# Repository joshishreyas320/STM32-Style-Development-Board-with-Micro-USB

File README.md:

# STM32-Style Development Board with Micro USB

> KiCad PCB Design | 2-Layer Board | ATmega328P-M + Micro USB

---

## Project Description
An Arduino-compatible MCU development board designed using **KiCad**, featuring an **ATmega328P-M** microcontroller, **Micro USB** interface for power and programming, and an **LM1117DT-5V** onboard voltage regulator. Dual 15-pin expansion headers provide full GPIO access in an Arduino-compatible footprint. Includes SMD resonator, power LED, and reset switch.

**Short Description (≤350 chars):**
> Arduino-compatible MCU development board with Micro USB interface, LM1117 5V regulation, dual 15-pin headers, and onboard LED+reset. Designed in KiCad with ATmega328P-M for embedded development use.

---

## Key Components

| Component | Description |
|-----------|-------------|
| **ATmega328P-M** | Core MCU – Arduino-compatible |
| **USB_B_Micro** | Micro USB connector for power and programming |
| **LM1117DT-5.0** | 5V LDO regulator from USB VBUS |
| **SMD Resonator (3-pin)** | Stable MCU clock source |
| **2× 15-pin Headers** | GPIO/power expansion (Arduino-style) |
| **Reset Switch** | Manual MCU reset |
| **LED** | Power indicator |
| **Decoupling Capacitors** | +3.3V and +5V rail filtering |

---

## Design Features
- Micro USB for both power supply and MCU programming
- LM1117DT-5.0 provides regulated 5V from USB VBUS
- ATmega328P-M with Arduino-compatible pinout
- SMD resonator for reliable clock without external components
- Compact 2-layer PCB with dual 15-pin expansion headers
- Onboard power LED and reset switch for user interaction

---

## Signal Flow
```
Micro USB Connector (VBUS / D+ / D-)
       ↓
  LM1117DT-5.0 – Voltage Regulator (5V)
       ↓
  ATmega328P-M – MCU
       ↓
  SMD Resonator ← Clock Source
  15-pin Dual Headers ← GPIO / Power Expansion
  LED ← Power Indicator
  Reset Switch ← Manual Reset
```

---

## Files Included
- Development_board_project_with_STM_components_and_Micro_USB.kicad_sch – Schematic
- Development_board_project_with_STM_components_and_Micro_USB.kicad_pcb – PCB Layout
- Gerber_File_Development_board_project_with_STM_components_and_Micro_USB.zip – Gerber files

---

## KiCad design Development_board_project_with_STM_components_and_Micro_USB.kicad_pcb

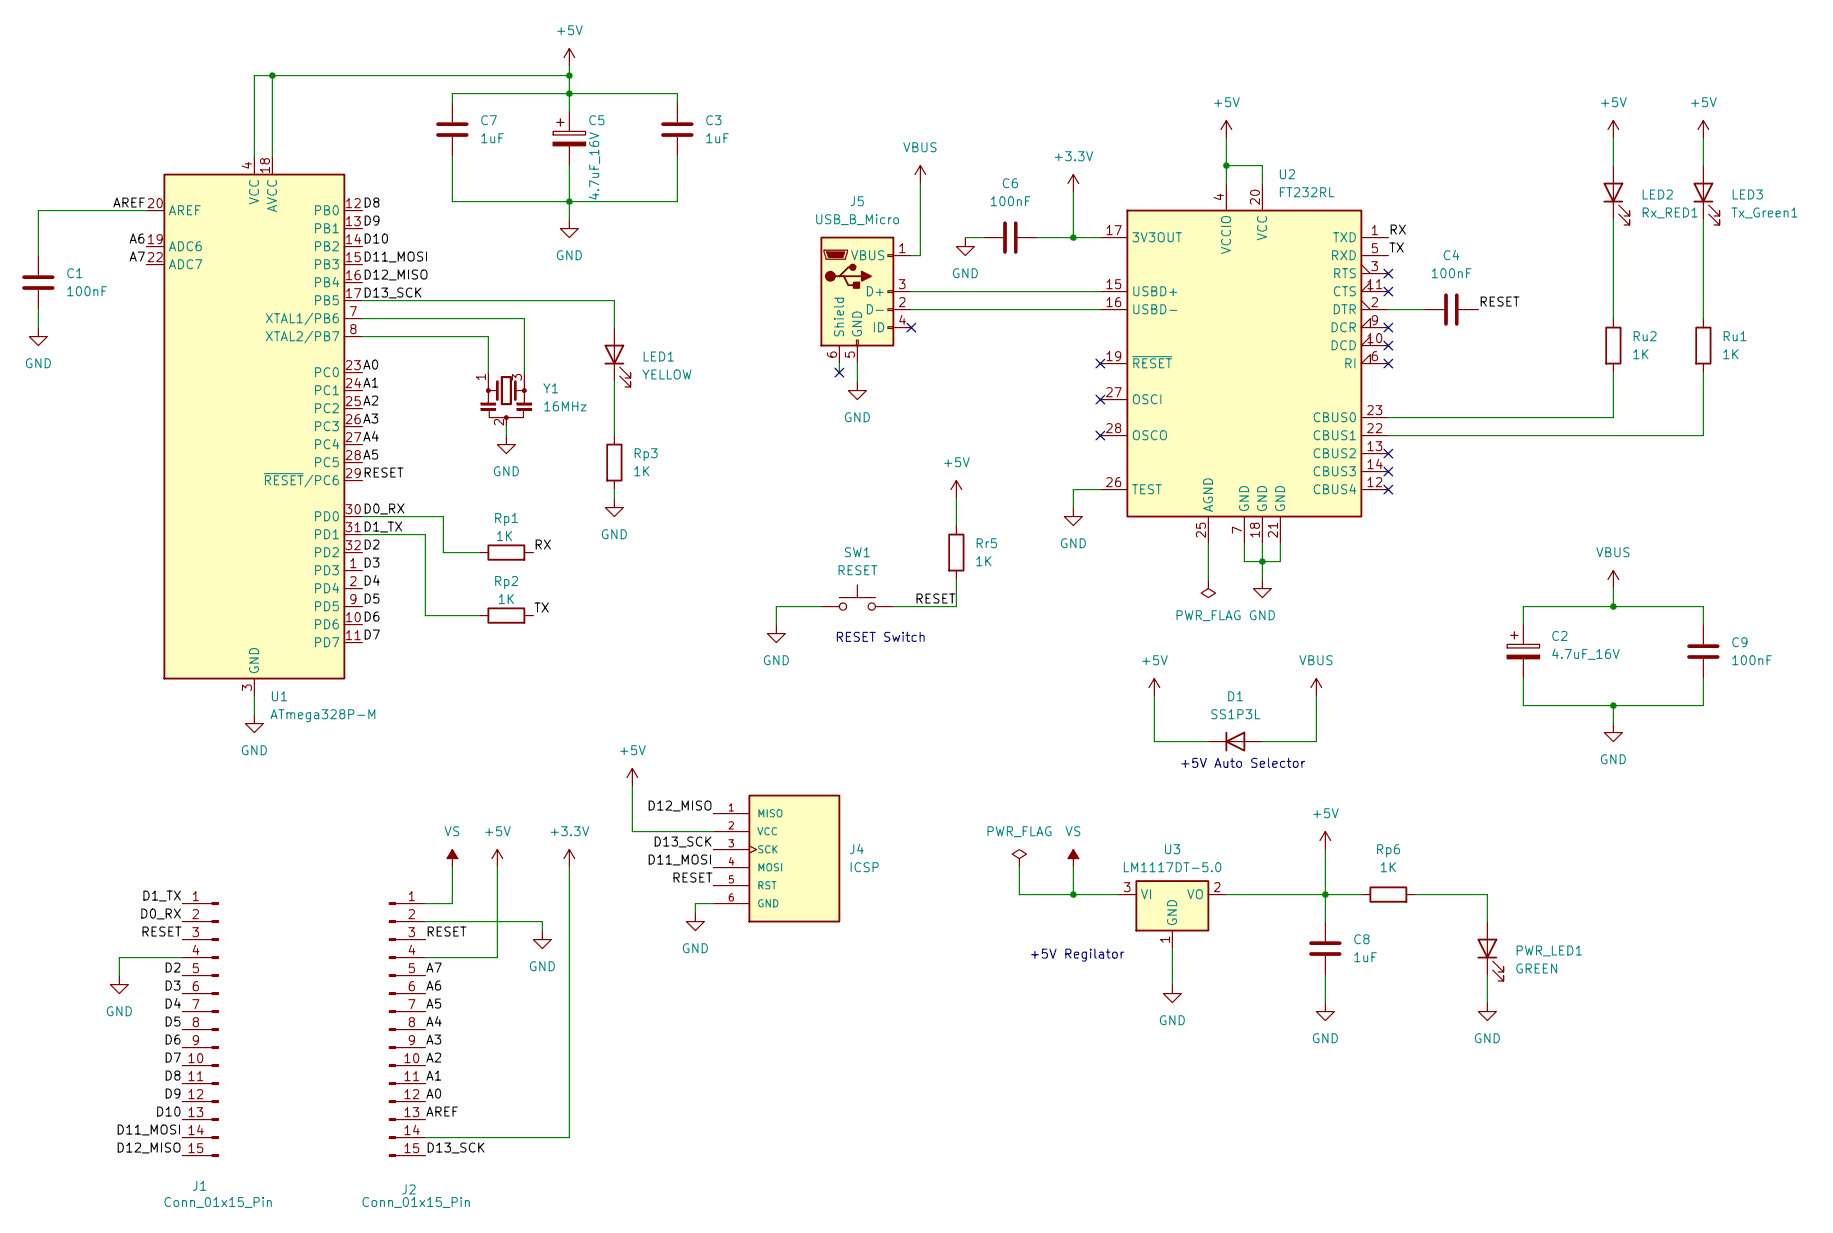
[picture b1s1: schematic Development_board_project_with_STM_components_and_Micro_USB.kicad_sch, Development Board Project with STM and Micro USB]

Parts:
C1, C4, C6, C9: 100nF; C_0805_2012Metric_Pad1.18x1.45mm_HandSolder
C2, C5: 4.7uF_16V; CP_EIA-3216-10_Kemet-I_HandSolder
C3, C7, C8: 1uF; C_0805_2012Metric_Pad1.18x1.45mm_HandSolder
D1: SS1P3L; D_SOD-123
J1, J2: Conn_01x15_Pin; PinHeader_1x15_P1.00mm_Vertical
J4: ICSP; PinHeader_2x03_P2.54mm_Vertical
J5: USB_B_Micro; USB_Mini-B_Lumberg_2486_01_Horizontal
LED1: YELLOW; LED_0603_1608Metric
LED2: Rx_RED1; LED_0603_1608Metric
LED3: Tx_Green1; LED_0603_1608Metric
PWR_LED1: GREEN; LED_0603_1608Metric
Rp1, Rp2, Rp3, Rp6: 1K; R_0805_2012Metric_Pad1.20x1.40mm_HandSolder
Rr5: 1K; R_0805_2012Metric_Pad1.20x1.40mm_HandSolder
Ru1, Ru2: 1K; R_0805_2012Metric_Pad1.20x1.40mm_HandSolder
SW1: RESET; SW_Push_1P1T_NO_E-Switch_TL3301NxxxxxG
U1: ATmega328P-M; QFN-32-1EP_5x5mm_P0.5mm_EP3.1x3.1mm
U2: FT232RL; SSOP-28_5.3x10.2mm_P0.65mm
U3: LM1117DT-5.0; TO-252-3_TabPin2
Y1: 16MHz; Crystal_SMD_3225-4Pin_3.2x2.5mm_HandSoldering

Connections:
+3.3V: C6.2, J2.14, U2.17 (3V3OUT)
+5V: C3.1, C5.1, C7.1, C8.1, D1.1 (K), J2.4, J4.2 (VCC), LED2.2 (A), LED3.2 (A), Rp6.1, Rr5.1, U1.4 (VCC), U1.6 (VCC), U1.18 (AVCC), U2.4 (VCCIO), U2.20 (VCC), U3.2 (VO)
/A0: J2.12, U1.23 (PC0)
/A1: J2.11, U1.24 (PC1)
/A2: J2.10, U1.25 (PC2)
/A3: J2.9, U1.26 (PC3)
/A4: J2.8, U1.27 (PC4)
/A5: J2.7, U1.28 (PC5)
/A6: J2.6, U1.19 (ADC6)
/A7: J2.5, U1.22 (ADC7)
/AREF: C1.1, J2.13, U1.20 (AREF)
/D0_RX: J1.2, Rp1.1, U1.30 (PD0)
/D1_TX: J1.1, Rp2.1, U1.31 (PD1)
/D2: J1.5, U1.32 (PD2)
/D3: J1.6, U1.1 (PD3)
/D4: J1.7, U1.2 (PD4)
/D5: J1.8, U1.9 (PD5)
/D6: J1.9, U1.10 (PD6)
/D7: J1.10, U1.11 (PD7)
/D8: J1.11, U1.12 (PB0)
/D9: J1.12, U1.13 (PB1)
/D10: J1.13, U1.14 (PB2)
/D11_MOSI: J1.14, J4.4 (MOSI), U1.15 (PB3)
/D12_MISO: J1.15, J4.1 (MISO), U1.16 (PB4)
/D13_SCK: J2.15, J4.3 (SCK), LED1.2 (A), U1.17 (PB5)
/RESET: C4.2, J1.3, J2.3, J4.5 (RST), Rr5.2, SW1.2, U1.29 (~RESET/PC6)
/RX: Rp1.2, U2.1 (TXD)
/TX: Rp2.2, U2.5 (RXD)
GND: C1.2, C2.2, C3.2, C5.2, C6.1, C7.2, C8.2, C9.2, J1.4, J2.2, J4.6 (GND), J5.5 (GND), PWR_LED1.1 (K), Rp3.2, SW1.1, U1.3 (GND), U1.5 (GND), U1.21 (GND), U1.33 (GND), U2.7 (GND), U2.18 (GND), U2.21 (GND), U2.26 (TEST), U3.1 (GND), Y1.2
unnamed: J5.3 (D+), U2.15 (USBD+)
unnamed: J5.2 (D-), U2.16 (USBD-)
unnamed: LED1.1 (K), Rp3.1
unnamed: LED2.1 (K), Ru2.1
unnamed: LED3.1 (K), Ru1.1
unnamed: PWR_LED1.2 (A), Rp6.2
unnamed: U1.7 (XTAL1/PB6), Y1.3
unnamed: U1.8 (XTAL2/PB7), Y1.1
unnamed: Ru2.2, U2.23 (CBUS0)
unnamed: Ru1.2, U2.22 (CBUS1)
unnamed: C4.1, U2.2 (DTR)
VBUS: C2.1, C9.1, D1.2 (A), J5.1 (VBUS)
VS: J2.1, U3.3 (VI)

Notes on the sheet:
RESET Switch
+5V Auto Selector
+5V Regilator

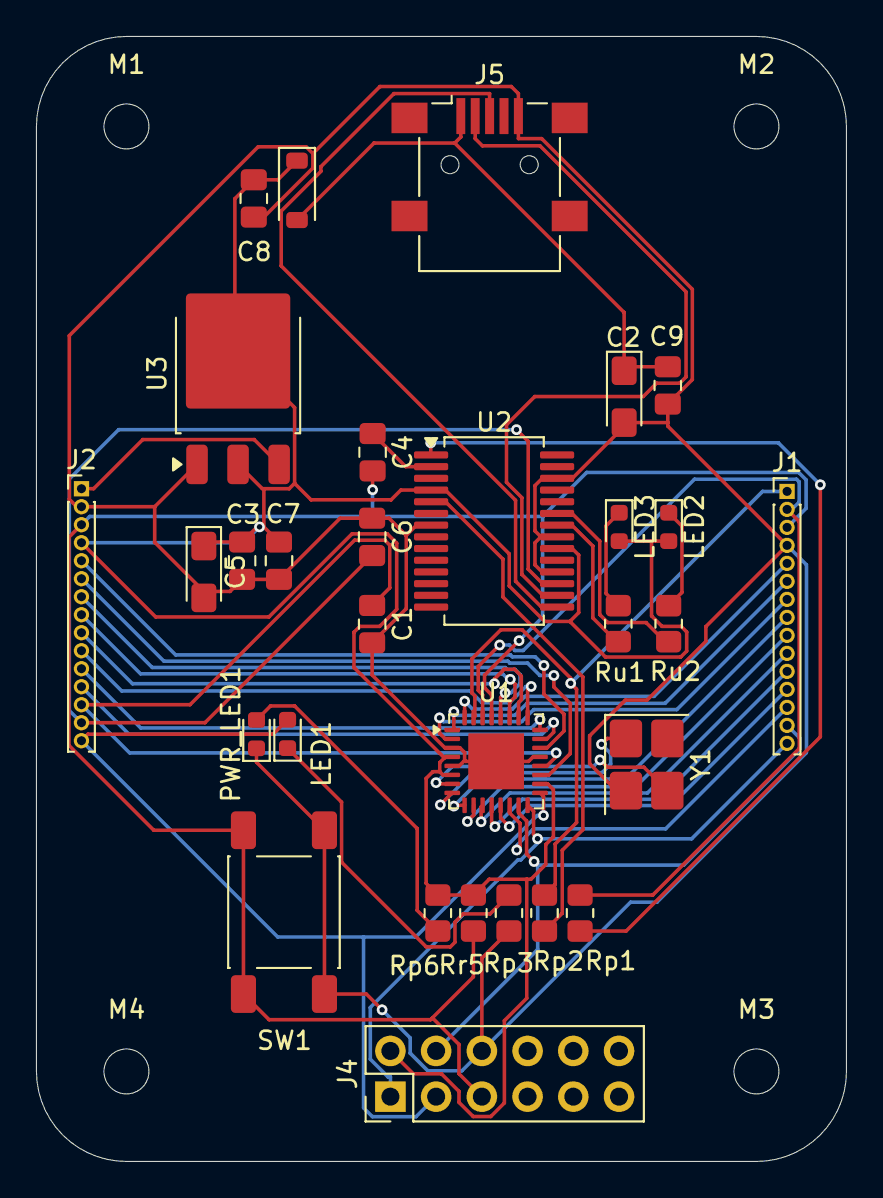
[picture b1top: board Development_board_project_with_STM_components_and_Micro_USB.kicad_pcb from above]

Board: 2 copper layers, 45.0 x 62.5 mm, 34 parts (0 on the bottom side), 42 nets.

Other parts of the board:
M1, M2, M3, M4: MountingHole_2.5mm

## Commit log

2026-06-06 Fix formatting of file list in README.md
